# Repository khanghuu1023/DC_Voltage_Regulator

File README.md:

# DC VOLTAGE REGULATOR 
I made this linear voltage regulator using an **L317T** IC, whose output voltage range is controlled and monitored by a potentiometer. The reason for making this board is to power my gernal purpose opamps used for various circuit testing. 

## PCB IN EAGLE:

## ASSEMBLE THE PCB:

The board is being manufactured by jclpcb and will be here in a few days. 

QUICK UPDATE: The boards finally arrived!!

I realized there is an issue with the silkscreen layer, the size of the names and values is too small, after I submitted my order on JCLPCB. I should have made them bigger.

I will post images of the completly soldered board later on

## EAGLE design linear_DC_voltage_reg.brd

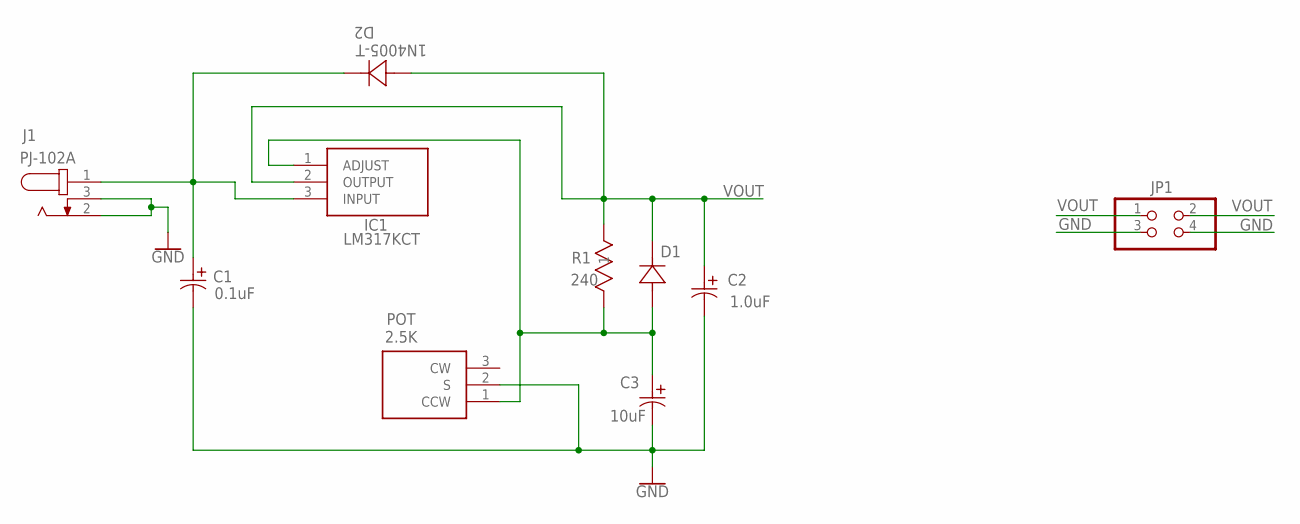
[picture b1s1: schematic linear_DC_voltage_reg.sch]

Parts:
C1: 0.1uF; CAP_C322_KEM
C2: 1.0uF; CAP_C322_KEM
C3: 10uF; CAP_C322_KEM
D1, D2: 1N4005-T; DO-41_DIO
IC1: LM317KCT; TO254P465X1016X1883-3P
J1: PJ-102A; CUI_PJ-102A
JP1: PINHD-2X2; 2X02
POT: 2.5K; P160KN0FC18C2K5
R1: 240; STA_CFM12_STP

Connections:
GND: C1.2, C2.2, C3.2, J1.2, J1.3, JP1.3, JP1.4, POT.2 (S)
VADJ: C3.1, D1.2, IC1.1 (ADJUST), POT.1 (CCW), R1.2
VIN: C1.1, D2.1, IC1.3 (INPUT), J1.1
VOUT: C2.1, D1.1, D2.2, IC1.2 (OUTPUT), JP1.1, JP1.2, R1.1

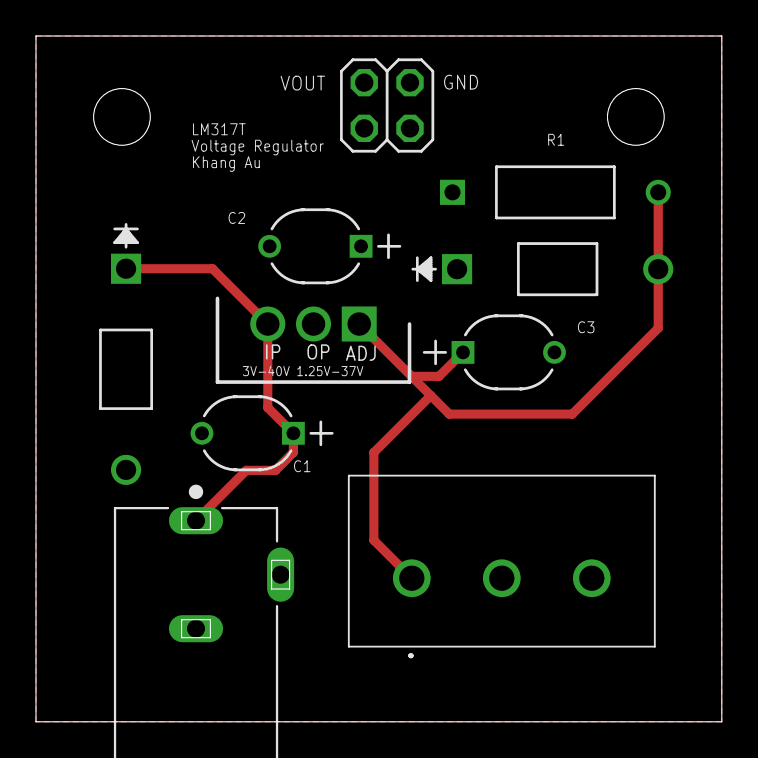
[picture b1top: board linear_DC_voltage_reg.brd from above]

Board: 2 copper layers, 38.1 x 38.1 mm, 10 parts (0 on the bottom side), 4 nets.

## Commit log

2021-08-24 first
    abc
2021-09-02 Create PCB_ARRIVED.jpg
    The PCBs finally arrived !!!!
2021-09-02 The PCBs finally arrived!!!!
2021-09-02 PCBs finally arrived!!

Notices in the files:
parts and their libraries:
COPYRIGHT: Copyright (C) 2021 Ultra Librarian. All rights reserved.
SparkFun-PowerSymbols: Licensing: Creative Commons ShareAlike 4.0 International - https://creativecommons.org/licenses/by-sa/4.0
